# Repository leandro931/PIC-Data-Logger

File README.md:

# PIC-Data-Logger
A data logger based on PIC18F4550 for development

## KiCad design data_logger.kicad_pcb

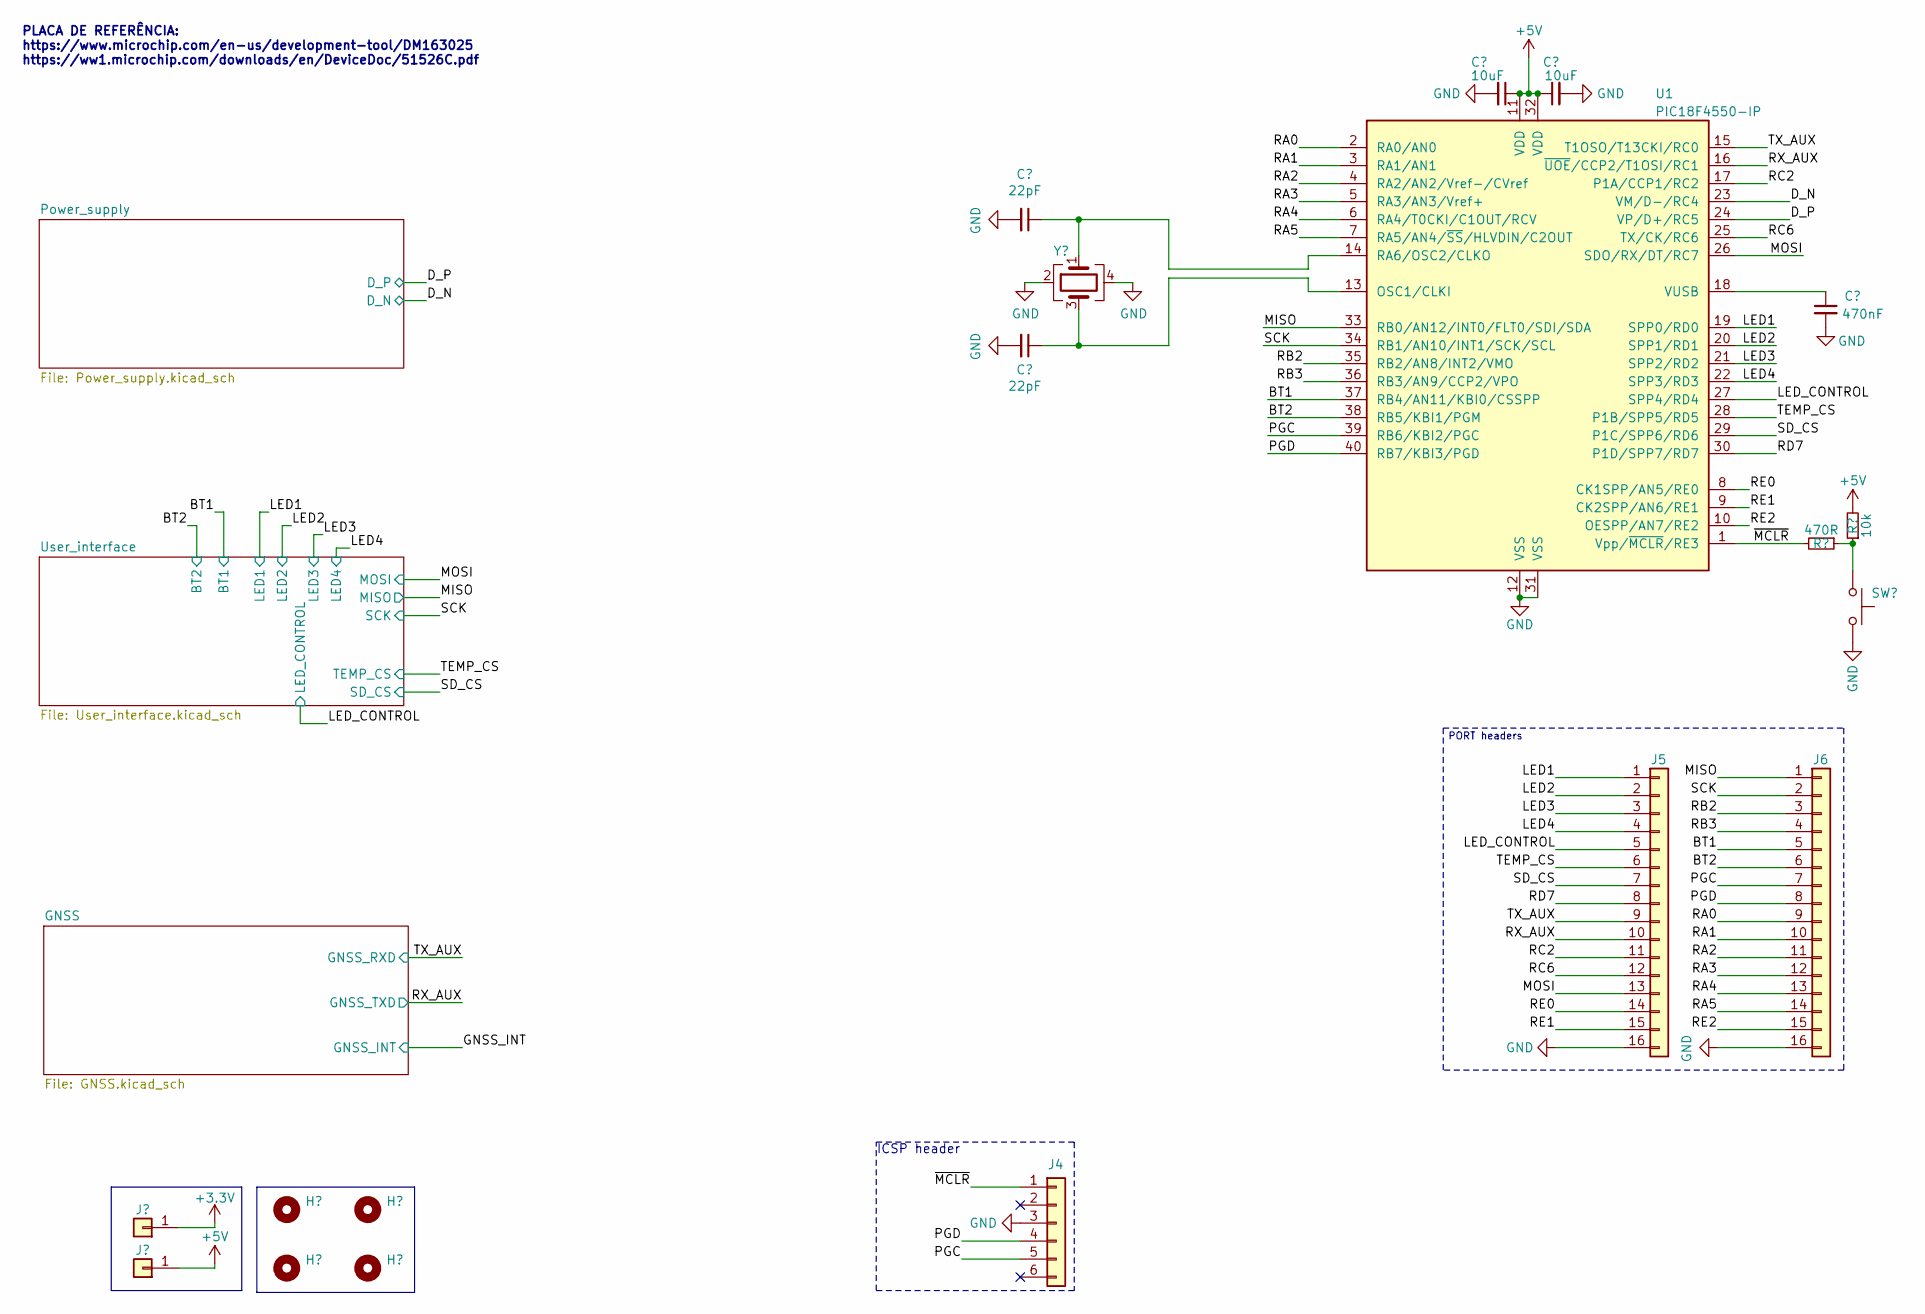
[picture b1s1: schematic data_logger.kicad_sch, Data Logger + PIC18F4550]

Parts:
C1, C2: 22pF; C_0402_1005Metric; Voltage rating greater than or equal to 50V; Tolerance less than or equal to ±1%
C3, C4: 10uF; C_0603_1608Metric; Tolerance less than or equal to ±10%; Voltage rating greater than or equal to 50V
C5: 470nF; C_0603_1608Metric; Tolerance less than or equal to ±10%; Voltage rating greater than or equal to 50V
H1, H2, H3, H4: MountingHole; MountingHole_2.2mm_M2
J1, J2: PinHeader_01x01_P2.54mm_Vertical; PinHeader_1x01_P2.54mm_Vertical
J4: PinHeader_01x06_P2.54mm_Vertical; PinHeader_1x06_P2.54mm_Vertical
J5, J6: Conn_01x16; PinSocket_1x16_P2.54mm_Vertical
R1: 470R; R_0402_1005Metric; Power rating greater than or equal to 1/10W; Tolerance less than or equal to ±5%
R2: 10k; R_0402_1005Metric; Power rating greater than or equal to 1/10W; Tolerance less than or equal to ±5%
SW1: SW_Push_Shouhan_TS3315A; SW_Push_SPST_TopActuated_Shouhan_TS3315A; Power rating 50mA@12VDC; Manufacturer P/N TS3315A; lcsc# C412367
U1: PIC18F4550-IP; DIP-40_W15.24mm
Y1: X1E0000210624; Crystal_SMD_3225-4Pin_3.2x2.5mm; Manufacturer P/N Q24FA20H00431; lcsc# C255914

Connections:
+3.3V: J1.1; also elsewhere on the board
+5V: C3.1, C4.1, J2.1, R2.2, U1.11 (VDD), U1.32 (VDD); also elsewhere on the board
/BT1: J6.5, U1.37 (RB4/AN11/KBI0/CSSPP); also elsewhere on the board
/BT2: J6.6, U1.38 (RB5/KBI1/PGM); also elsewhere on the board
/D_N: U1.23 (VM/D-/RC4); also elsewhere on the board
/D_P: U1.24 (VP/D+/RC5); also elsewhere on the board
/LED1: J5.1, U1.19 (SPP0/RD0); also elsewhere on the board
/LED2: J5.2, U1.20 (SPP1/RD1); also elsewhere on the board
/LED3: J5.3, U1.21 (SPP2/RD2); also elsewhere on the board
/LED4: J5.4, U1.22 (SPP3/RD3); also elsewhere on the board
/LED_CONTROL: J5.5, U1.27 (SPP4/RD4); also elsewhere on the board
/MISO: J6.1, U1.33 (RB0/AN12/INT0/FLT0/SDI/SDA); also elsewhere on the board
/MOSI: J5.13, U1.26 (SDO/RX/DT/RC7); also elsewhere on the board
/PGC: J4.5, J6.7, U1.39 (RB6/KBI2/PGC)
/PGD: J4.4, J6.8, U1.40 (RB7/KBI3/PGD)
/RA0: J6.9, U1.2 (RA0/AN0)
/RA1: J6.10, U1.3 (RA1/AN1)
/RA2: J6.11, U1.4 (RA2/AN2/Vref-/CVref)
/RA3: J6.12, U1.5 (RA3/AN3/Vref+)
/RA4: J6.13, U1.6 (RA4/T0CKI/C1OUT/RCV)
/RA5: J6.14, U1.7 (RA5/AN4/~SS/HLVDIN/C2OUT)
/RB2: J6.3, U1.35 (RB2/AN8/INT2/VMO)
/RB3: J6.4, U1.36 (RB3/AN9/CCP2/VPO)
/RC2: J5.11, U1.17 (P1A/CCP1/RC2)
/RC6: J5.12, U1.25 (TX/CK/RC6)
/RD7: J5.8, U1.30 (P1D/SPP7/RD7)
/RE0: J5.14, U1.8 (CK1SPP/AN5/RE0)
/RE1: J5.15, U1.9 (CK2SPP/AN6/RE1)
/RE2: J6.15, U1.10 (OESPP/AN7/RE2)
/RX_AUX: J5.10, U1.16 (~UOE/CCP2/T1OSI/RC1); also elsewhere on the board
/SCK: J6.2, U1.34 (RB1/AN10/INT1/SCK/SCL); also elsewhere on the board
/SD_CS: J5.7, U1.29 (P1C/SPP6/RD6); also elsewhere on the board
/TEMP_CS: J5.6, U1.28 (P1B/SPP5/RD5); also elsewhere on the board
/TX_AUX: J5.9, U1.15 (T1OSO/T13CKI/RC0); also elsewhere on the board
/~MCLR: J4.1, R1.2, U1.1 (Vpp/~MCLR/RE3)
GND: C1.2, C2.2, C3.2, C4.2, C5.2, J4.3, J5.16, J6.16, SW1.2, U1.12 (VSS), U1.31 (VSS), Y1.2, Y1.4; also elsewhere on the board
unnamed: R1.1, R2.1, SW1.1
unnamed: C2.1, U1.13 (OSC1/CLKI), Y1.3
unnamed: C1.1, U1.14 (RA6/OSC2/CLKO), Y1.1
unnamed: C5.1, U1.18 (VUSB)

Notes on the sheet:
ICSP header
PLACA DE REFERÊNCIA: https://www.microchip.com/en-us/development-tool/DM163025 https://ww1.microchip.com/downloads/en/DeviceDoc/51526C.pdf
PORT headers

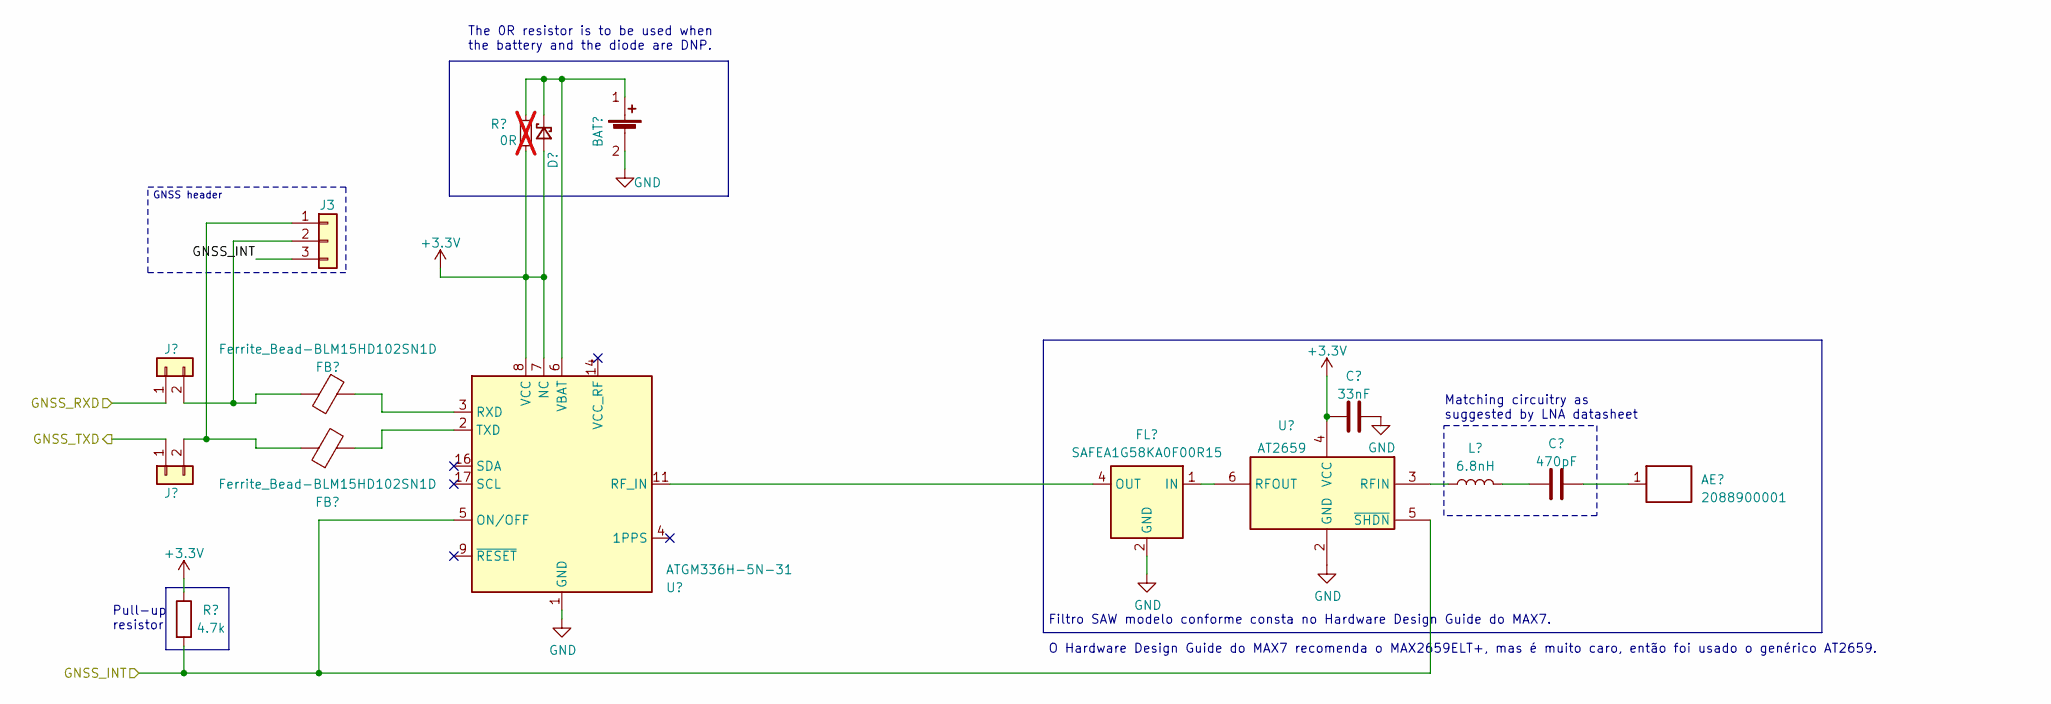
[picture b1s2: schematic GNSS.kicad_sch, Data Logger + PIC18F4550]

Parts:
AE1: 2088900001; Molex-2088900001-GPS-Ceramic_Antenna; Power rating 2W max. (CW); Manufacturer P/N 2088900001; mouser# 538-208890-0001
BAT1: Battery_Seiko_MS412FE_D4.8mm; Manufacturer P/N MS412FE-FL26E; digikey# 728-1053-ND
C6: 33nF; C_0402_1005Metric; Tolerance less than or equal to ±10%; Voltage rating greater than or equal to 16V
C7: 470pF; C_0402_1005Metric; Tolerance less than or equal to ±10%; Voltage rating greater than or equal to 16V
D1: CDBQC0240LR-HF; D_0402_1006Metric; Manufacturer P/N CDBQC0240LR-HF; digikey# 641-1888-1-ND
FB1, FB2: Ferrite_Bead-BLM15HD102SN1D; L_0402_1005Metric; Manufacturer P/N BLM15HD102SN1D
FL1: SAFEA1G58KA0F00R15; Filter_1109-5_1.1x0.9mm; Manufacturer P/N SAFEA1G58KA0F00R15; lcsc# C91641
J3: Conn_01x03; PinSocket_1x03_P2.54mm_Vertical
J7, J8: PinHeader_01x02_P2.54mm_Vertical; PinHeader_1x02_P2.54mm_Vertical
L1: 6.8nH; L_0402_1005Metric
R3: 4.7k; R_0402_1005Metric; Power rating 1/8W; Tolerance ±1%; Manufacturer P/N RS-05K4701FT; LCSC P/N C115319
R4: 0R; R_0402_1005Metric; Power rating greater than or equal to 1/16W; Tolerance Jumper; Manufacturer P/N CRCW04020000Z0ED; digikey# 541-0.0JCT-ND; not fitted
U2: ATGM336H-5N-31; atgm336h; Manufacturer P/N ATGM336H-5N31
U3: AT2659; lcsc# C92450

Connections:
+3.3V: C6.1, D1.2 (A), R3.1, R4.2, U2.7 (NC), U2.8 (VCC), U3.4 (VCC); also elsewhere on the board
/GNSS_INT: J3.3, R3.2, U2.5 (ON/OFF), U3.5 (~SHDN)
/RX_AUX: J8.1; also elsewhere on the board
/TX_AUX: J7.1; also elsewhere on the board
GND: BAT1.2 (-), C6.2, FL1.2 (GND), FL1.3 (GND), FL1.5 (GND), U2.1 (GND), U2.10 (GND), U2.12 (GND), U3.1 (GND), U3.2 (GND); also elsewhere on the board
unnamed: AE1.1, C7.2
unnamed: BAT1.1 (+), D1.1 (K), R4.1, U2.6 (VBAT)
unnamed: C7.1, L1.2
unnamed: FL1.1 (IN), U3.6 (RFOUT)
unnamed: FL1.4 (OUT), U2.11 (RF_IN)
unnamed: FB2.1, J3.1, J8.2
unnamed: FB1.2, J3.2, J7.2
unnamed: FB1.1, U2.3 (RXD)
unnamed: FB2.2, U2.2 (TXD)
unnamed: L1.1, U3.3 (RFIN)

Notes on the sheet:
Filtro SAW modelo conforme consta no Hardware Design Guide do MAX7. O Hardware Design Guide do MAX7 recomenda o MAX2659ELT+, mas é muito caro, então foi usado o genérico AT2659.
The 0R resistor is to be used when the battery and the diode are DNP.
Matching circuitry as suggested by LNA datasheet
Pull-up resistor
GNSS header

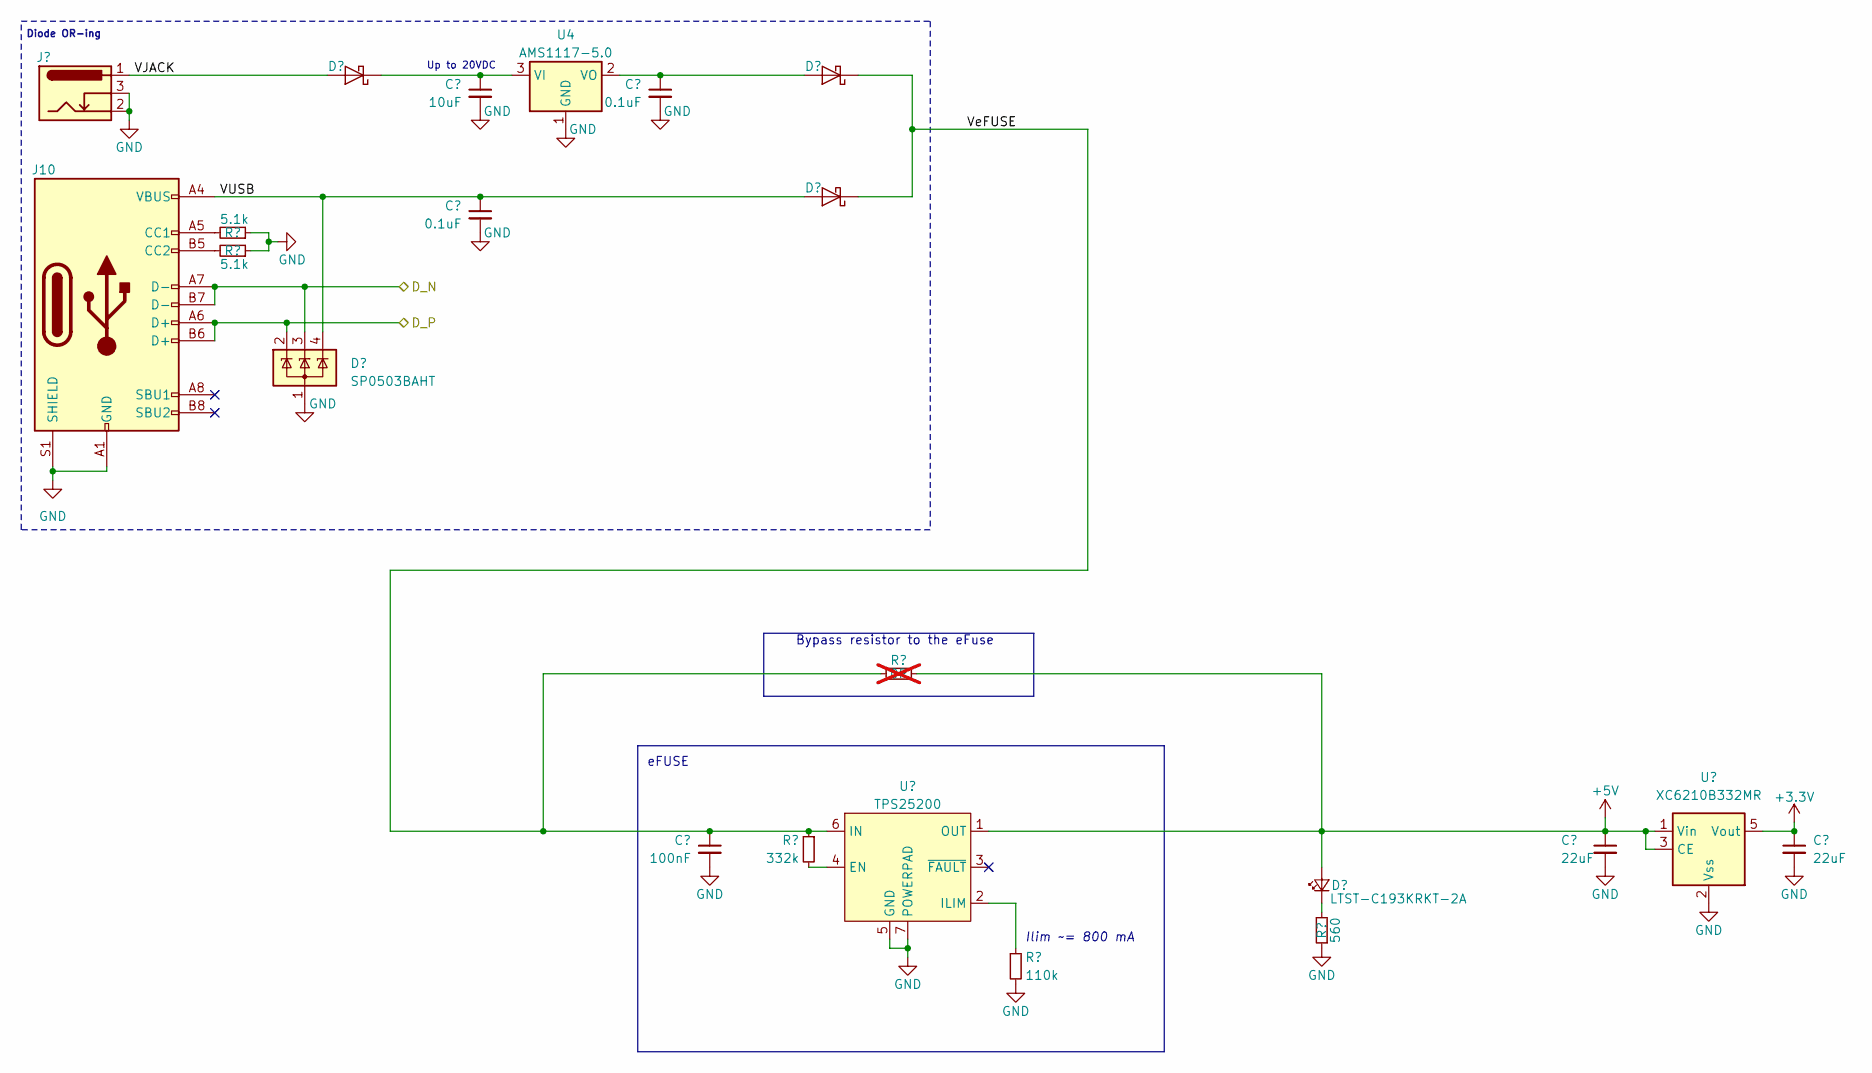
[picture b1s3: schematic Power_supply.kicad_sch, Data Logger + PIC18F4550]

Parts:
C8: 10uF; C_0603_1608Metric; Tolerance less than or equal to ±10%; Voltage rating greater than or equal to 50V
C9, C10: 0.1uF; C_0603_1608Metric; Tolerance less than or equal to ±10%; Voltage rating greater than or equal to 50V
C11: 100nF; C_0603_1608Metric; Tolerance less than or equal to ±10%; Voltage rating greater than or equal to 50V; Manufacturer P/N 08055C104KAT2A; digikey# 478-1395-1-ND
C12, C13: 22uF; C_0603_1608Metric; Tolerance less than or equal to ±20%; Voltage rating greater than or equal to 16V; Manufacturer P/N 1206YD226MAT2A; digikey# 478-5332-1-ND
D2: SP0503BAHT; SOT-143
D3, D4, D5: DSK24_K24; Microdiode_SOD-123FL; Manufacturer P/N DSK24 K24; lcsc# C64890
D6: LTST-C193KRKT-2A; LED_0603_1608Metric; Manufacturer P/N LTST-C193KRKT-2A; digikey# 160-1909-1-ND
J9: Barrel_Jack_Switch_CUI_PJ-102AH; BarrelJack_CUI_PJ-102AH_Horizontal; Manufacturer P/N PJ-102AH; digikey# CP-102AH-ND
J10: USB_C_Receptacle; USB_C_Receptacle_GCT_USB4105-xx-A_16P_TopMnt_Horizontal; Manufacturer P/N KH-TYPE-C-16P; lcsc# C709357
R5, R6: 5.1k; R_0603_1608Metric; Power rating greater than or equal to 1/10W; Tolerance less than or equal to ±1%; Manufacturer P/N CRCW0603332KFKEA; digikey# 541-332KHCT-ND
R7: 332k; R_0603_1608Metric; Power rating greater than or equal to 1/10W; Tolerance less than or equal to ±1%; Manufacturer P/N CRCW0603332KFKEA; digikey# 541-332KHCT-ND
R8: 0R; R_0805_2012Metric; Power rating greater than or equal to 1/8W; Tolerance Jumper; Manufacturer P/N RMCF0805ZT0R00; digikey# RMCF0805ZT0R00CT-ND; not fitted
R9: 110k; R_0805_2012Metric; Power rating greater than or equal to 1/8W; Tolerance less than or equal to ±0,1%; Manufacturer P/N RT0805BRD07169KL; digikey# YAG4836CT-ND
R10: 560; R_0402_1005Metric; Power rating greater than or equal to 1/10W; Tolerance less than or equal to ±5%; Manufacturer P/N RC0603JR-072KL; digikey# 311-2.0KGRCT-ND
U4: AMS1117-5.0; SOT-223-3_TabPin2
U5: TPS25200; Texas_DRV0006A_WSON-6-1EP_2x2mm_P0.65mm_EP1x1.6mm_ThermalVi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; Manufacturer P/N TPS25200DRVR; digikey# 296-37842-1-ND
U6: XC6210B332MR; Torex_SOT-25; Manufacturer P/N XC6210B332MR; digikey# 893-1075-1-ND

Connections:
+3.3V: C13.1, U6.5 (Vout); also elsewhere on the board
+5V: C12.1, D6.2 (A), R8.2, U5.1 (OUT), U6.1 (Vin), U6.3 (CE); also elsewhere on the board
/D_N: D2.3 (K), J10.A7 (D-), J10.B7 (D-); also elsewhere on the board
/D_P: D2.2 (K), J10.A6 (D+), J10.B6 (D+); also elsewhere on the board
/Power_supply/VJACK: D3.2 (A), J9.1
/Power_supply/VUSB: C9.1, D2.4 (K), D5.2 (A), J10.A4 (VBUS), J10.A9 (VBUS), J10.B4 (VBUS), J10.B9 (VBUS)
/Power_supply/VeFUSE: C11.1, D4.1 (K), D5.1 (K), R7.1, R8.1, U5.6 (IN)
GND: C8.2, C9.2, C10.2, C11.2, C12.2, C13.2, D2.1 (A), J9.2, J9.3, J10.A1 (GND), J10.A12 (GND), J10.B1 (GND), J10.B12 (GND), J10.S1 (SHIELD), R5.1, R6.1, R9.2, R10.1, U4.1 (GND), U5.5 (GND), U5.7 (POWERPAD), U6.2 (Vss); also elsewhere on the board
unnamed: C8.1, D3.1 (K), U4.3 (VI)
unnamed: C10.1, D4.2 (A), U4.2 (VO)
unnamed: D6.1 (K), R10.2
unnamed: J10.A5 (CC1), R5.2
unnamed: J10.B5 (CC2), R6.2
unnamed: R7.2, U5.4 (EN)
unnamed: R9.1, U5.2 (ILIM)

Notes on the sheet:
eFUSE
Ilim ~= 800 mA
Up to 20VDC
Diode OR-ing
Bypass resistor to the eFuse

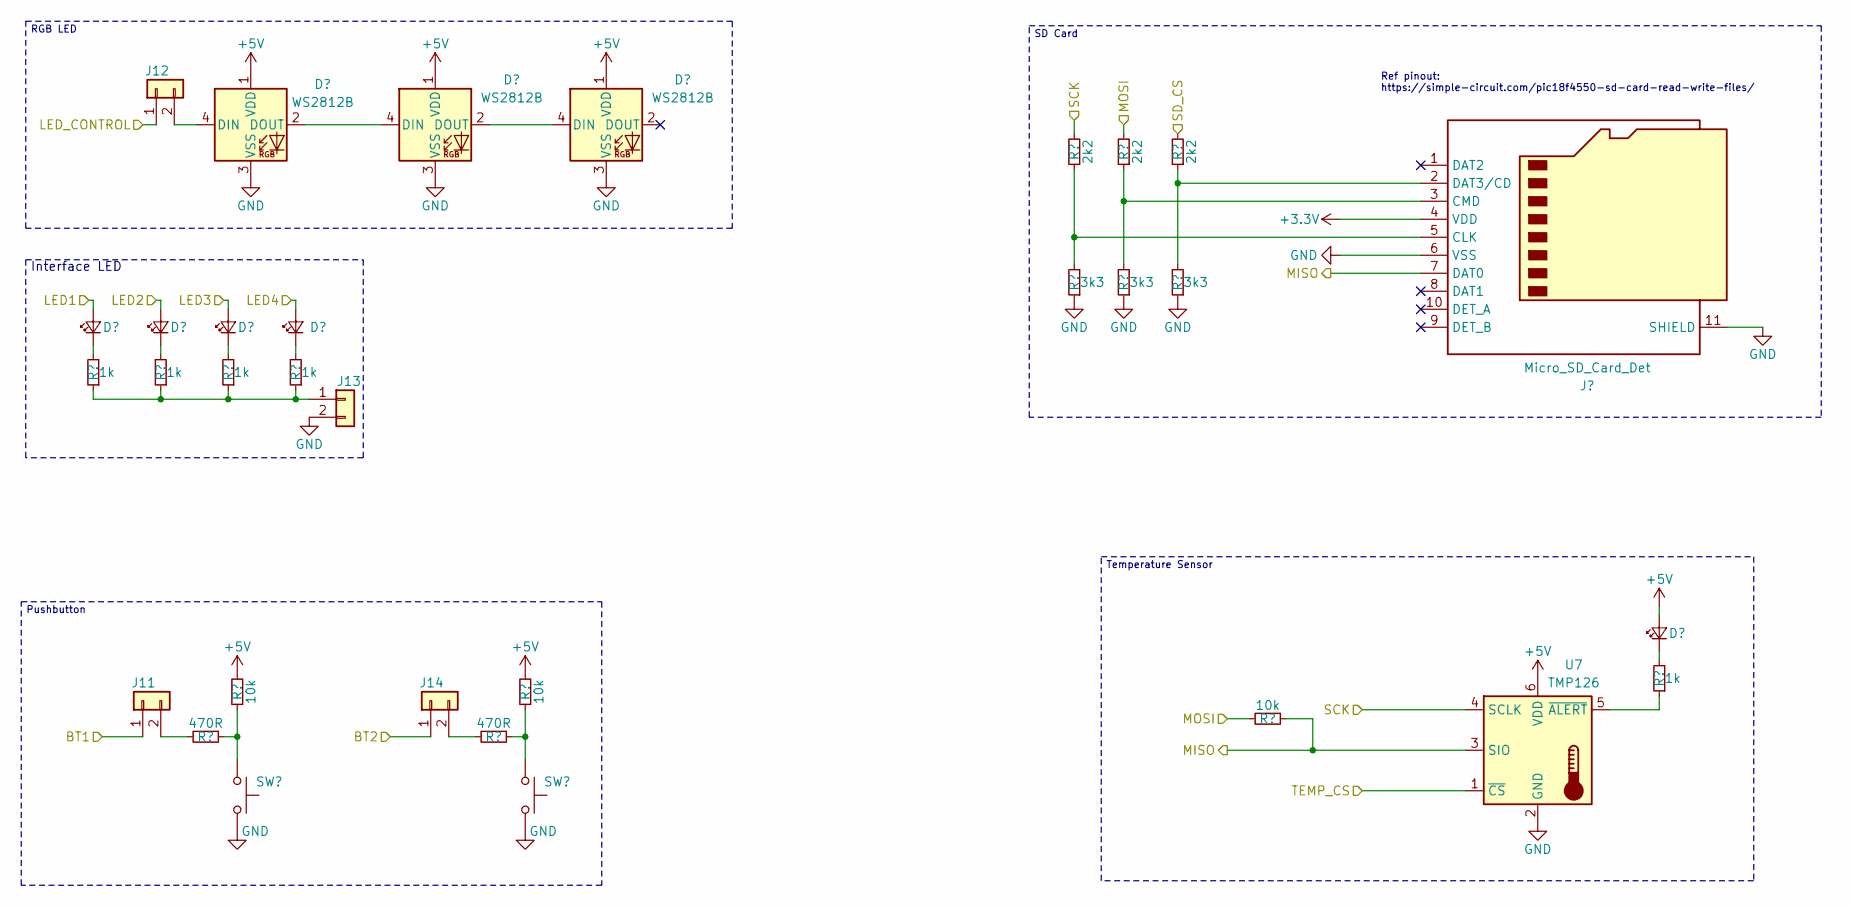
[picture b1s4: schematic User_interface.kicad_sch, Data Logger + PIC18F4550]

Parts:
D7, D8, D9, D10, D14: LTST-C193KRKT-2A; LED_0603_1608Metric; Manufacturer P/N LTST-C193KRKT-2A; digikey# 160-1909-1-ND
D11, D12, D13: WS2812B; LED_WS2812B_PLCC4_5.0x5.0mm_P3.2mm; Manufacturer P/N WS2812B
J11, J12, J13, J14: PinHeader_01x02_P2.54mm_Vertical; PinHeader_1x02_P2.54mm_Vertical
J15: Micro_SD_Card_Det; SDCARD_MOLEX_503398-1892; Manufacturer P/N 503398-1892; digikey# WM11190CT-ND
R11, R12, R14, R16, R26: 1k; R_0402_1005Metric; Power rating greater than or equal to 1/10W; Tolerance less than or equal to ±5%
R13, R17: 470R; R_0402_1005Metric; Power rating greater than or equal to 1/10W; Tolerance less than or equal to ±5%
R15, R18: 10k; R_0402_1005Metric; Power rating greater than or equal to 1/10W; Tolerance less than or equal to ±5%
R19, R21, R23: 2k2; R_0805_2012Metric; Power rating greater than or equal to 1/8W; Tolerance Jumper
R20, R22, R24: 3k3; R_0402_1005Metric; Power rating greater than or equal to 1/10W; Tolerance less than or equal to ±5%
R25: 10k; R_0805_2012Metric; Power rating greater than or equal to 1/8W; Tolerance Jumper
SW2, SW3: SW_Push_Shouhan_TS3315A; SW_Push_SPST_TopActuated_Shouhan_TS3315A; Power rating 50mA@12VDC; Manufacturer P/N TS3315A; lcsc# C412367
U7: TMP126; pSemi_SC-70-6; Manufacturer # TMP126

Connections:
+3.3V: J15.4 (VDD); also elsewhere on the board
+5V: D11.1 (VDD), D12.1 (VDD), D13.1 (VDD), D14.2 (A), R15.2, R18.2, U7.6 (VDD); also elsewhere on the board
/BT1: J11.1; also elsewhere on the board
/BT2: J14.1; also elsewhere on the board
/LED1: D7.2 (A); also elsewhere on the board
/LED2: D8.2 (A); also elsewhere on the board
/LED3: D9.2 (A); also elsewhere on the board
/LED4: D10.2 (A); also elsewhere on the board
/LED_CONTROL: J12.1; also elsewhere on the board
/MISO: J15.7 (DAT0), R25.1, U7.3 (SIO); also elsewhere on the board
/MOSI: R21.2, R25.2; also elsewhere on the board
/SCK: R19.2, U7.4 (SCLK); also elsewhere on the board
/SD_CS: R23.2; also elsewhere on the board
/TEMP_CS: U7.1 (~CS); also elsewhere on the board
GND: D11.3 (VSS), D12.3 (VSS), D13.3 (VSS), J13.2, J15.6 (VSS), J15.11 (SHIELD), R20.1, R22.1, R24.1, SW2.2, SW3.2, U7.2 (GND); also elsewhere on the board
unnamed: D7.1 (K), R11.2
unnamed: D8.1 (K), R12.2
unnamed: D9.1 (K), R14.2
unnamed: D10.1 (K), R16.2
unnamed: D11.4 (DIN), J12.2
unnamed: D11.2 (DOUT), D12.4 (DIN)
unnamed: D12.2 (DOUT), D13.4 (DIN)
unnamed: D14.1 (K), R26.2
unnamed: J11.2, R13.2
unnamed: J13.1, R11.1, R12.1, R14.1, R16.1
unnamed: J14.2, R17.2
unnamed: J15.5 (CLK), R19.1, R20.2
unnamed: J15.3 (CMD), R21.1, R22.2
unnamed: J15.2 (DAT3/CD), R23.1, R24.2
unnamed: R13.1, R15.1, SW2.1
unnamed: R17.1, R18.1, SW3.1
unnamed: R26.1, U7.5 (~ALERT)

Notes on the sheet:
Pushbutton
Ref pinout: https://simple-circuit.com/pic18f4550-sd-card-read-write-files/
Interface LED
Temperature Sensor
SD Card
RGB LED

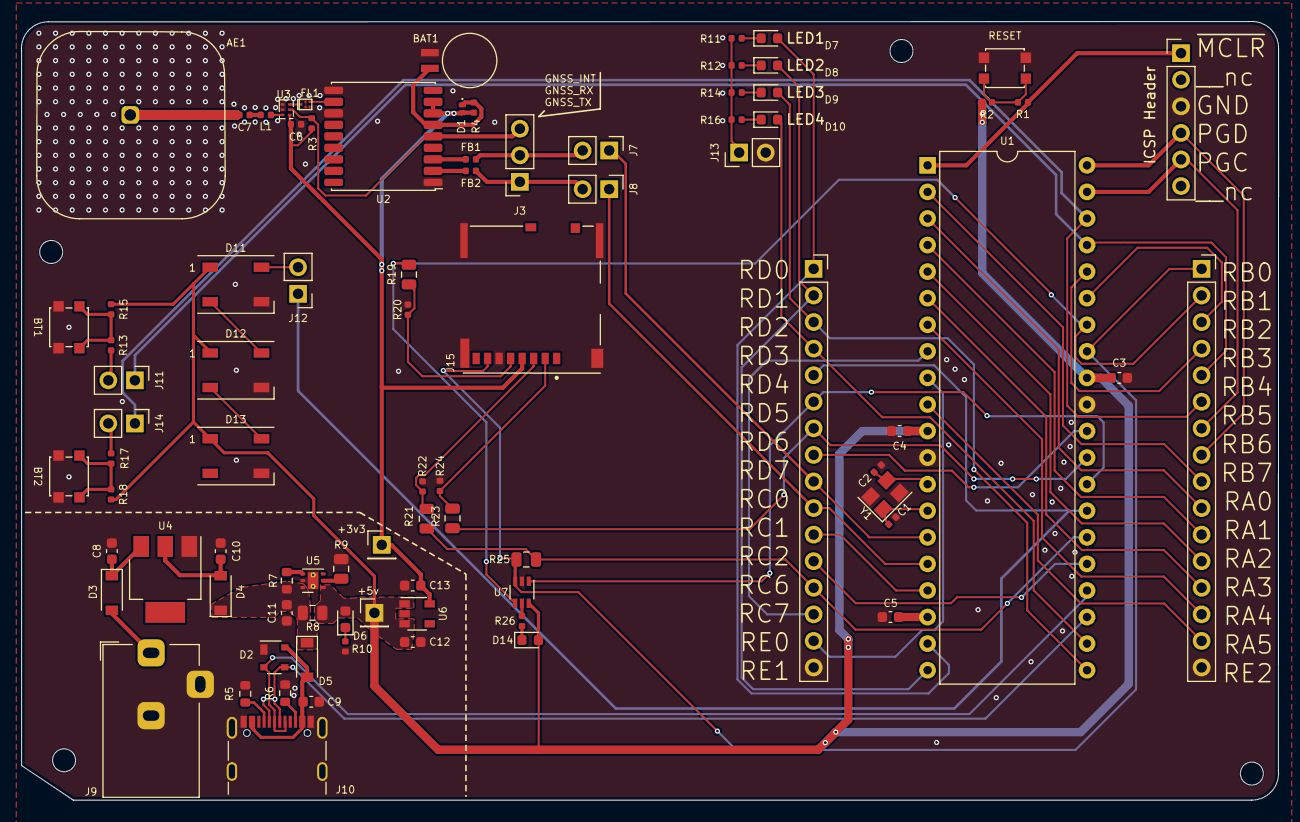
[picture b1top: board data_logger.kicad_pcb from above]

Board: 2 copper layers, 120.2 x 74.4 mm, 89 parts (0 on the bottom side), 78 nets.

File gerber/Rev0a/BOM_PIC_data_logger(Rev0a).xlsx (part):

Item | Qty | Reference(s) | To be assembled? | Value | Description | Manufacturer | Manufacturer P/N | Mounting type | Package | digikey# | lcsc# | mouser# | newark# | rs# | tme# | Datasheet
1 | 1 | AE1 | Yes | 2088900001 | GPS Ceramic Patch Antenna | Molex | 2088900001 |  |  | WM26214-ND |  | 538-208890-0001 | 84AC5252 |  |  | https://www.molex.com/content/dam/molex/molex-dot-com/produc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 | https://pt.aliexpress.com/item/1005004484929374.html?spm=a2g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
2 | 1 | BAT1 | Yes | MS412FE-FL26E | Coin, 4.8mm 3V Lithium Rechargeable Battery 1mAh (MS412FE is not reflowable. Pl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 | Seiko Instruments | MS412FE-FL26E | SMD |  | 728-1053-ND |  | 628-MS412FE-FL26E |  |  |  | https://www.sii.co.jp/en/me/datasheets/ms-rechargeable/ms412fe-5/
3 | 2 | C1, C2 | Yes | 22pF | Multilayer Ceramic Chip Capacitor 22pF | YAGEO | CC0402JRNPO7BN220 | SMD | 0402_1005Metric |  | C2175872 |  |  |  |  | https://datasheet.lcsc.com/lcsc/2202040800_YAGEO-CC0402JRNPO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
4 | 3 | C3, C4, C8 | Yes | 10uF | Multilayer Ceramic Chip Capacitor 10uF | YAGEO | CC0603MRX5R7BB106 | SMD | 0603_1608Metric |  | C109457 |  |  |  |  | https://datasheet.lcsc.com/lcsc/1811021340_YAGEO-CC0603MRX5R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
5 | 1 | C5 | Yes | 470nF | Multilayer Ceramic Chip Capacitor 470nF | YAGEO | CC0603KRX7R7BB474 | SMD | 0603_1608Metric |  | C106851
6 | 1 | C6 | Yes | 33nF | Multilayer Ceramic Chip Capacitor 33nF | YAGEO | CC0402FRNPO9BN330 | SMD | 0402_1005Metric |  | C327064
7 | 1 | C7 | Yes | 470pF | Multilayer Ceramic Chip Capacitor 470pF | YAGEO | CC0402JRNPO7BN471 | SMD | 0402_1005Metric |  | C526993
8 | 2 | C9, C10 | Yes | 0.1uF | Multilayer Ceramic Chip Capacitor 0.1uF | YAGEO | CS0603KRX7R8BB104 | SMD | 0603_1608Metric |  | C577419
9 | 1 | C11 | Yes | 100nF | Multilayer Ceramic Chip Capacitor 100nF | YAGEO | CC0603KRX7R9BB104 | SMD | 0603_1608Metric |  | C14663
10 | 2 | C12, C13 | Yes | 22uF | Multilayer Ceramic Chip Capacitor 22uF | YAGEO | CC0603MRX5R5BB226 | SMD | 0603_1608Metric |  | C109448
11 | 1 | D1 | Yes | CDBQC0240LR-HF | Diode 40 V 200mA Surface Mount 0402C/SOD-923F | Comchip Technology | CDBQC0240LR-HF | SMD | 0402/SOD-923F | 641-1888-2-ND | C3758513 |  |  |  |  | https://www.comchiptech.com/admin/files/product/CDBQC0240LR-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
12 | 1 | D2 | Yes | SP0503BAHTG | 8.5V Clamp Ipp Tvs Diode Surface Mount SOT-143-4 | Littelfuse | SP0503BAHTG | SMD | SOT-143 | SP0503BAHT-ND | C7074 |  |  |  |  | http://www.littelfuse.com/~/media/files/littelfuse/technical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
13 | 3 | D3, D4, D5 | Yes | DSK24 | Schottky Barrier Diodes 40V 2A 550mV @ 2A SOD-123FL | MDD (Microdiode Electronics) | DSK24 | SMD | SOD-123FL | 3372-DSK24TR-ND | C64890 |  |  |  |  | https://mm.digikey.com/Volume0/opasdata/d220001/medias/docus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
14 | 1 | D6 | Yes | LTST-C193KRKT-2A | LED (red) 0603_1608Metric | Lite-On Inc. | LTST-C193KRKT-2A | SMD | 0603_1608 | 160-1909-1-ND |  |  |  |  |  | https://mm.digikey.com/Volume0/opasdata/d220001/medias/docus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
15 | 4 | D7, D8, D9, D10 | Yes | LTST-C193TBKT-5A | LED (blue) 0603_1608Metric | Lite-On Inc. |  | SMD | 0603_1608 | 160-1827-6-ND | C125103
16 | 3 | D11, D12, D13 | Yes | WS2812B | Intelligent control LED | Wordlsemi | WS2812B | SMD | SMD5050 | 1568-COM-16347TR-ND | C2761795 |  |  |  |  | https://cdn-shop.adafruit.com/datasheets/WS2812B.pdf
17 | 1 | D14 | Yes | LTST-C190YKT | LED (yellow) 0603_1608Metric | Lite-On Inc. | LTST-C190YKT | SMD | 0603_1608 | 160-1184-6-ND | C125097
18 | 2 | FB1, FB2 | Yes | Ferrite_Bead-BLM15HD102SN1D | 1kÎ© @ 100MHz 250mA 1 1.25Î© 0402 Ferrite Beads RoHS | Murata Electronics | BLM15HD102SN1D | SMD | 0402_1005 | 490-4003-2-ND | C21516 | 81-BLM15HD102SN1D |  |  |  | https://datasheet.lcsc.com/szlcsc/1811091923_Murata-Electron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
19 | 1 | FL1 | Yes | SAFEA1G58KA0F00R15 | GNSS SAW filter | Murata | SAFEA1G58KA0F00R15 | SMD | QCS5P |  | C91641 |  |  |  |  | https://datasheet.lcsc.com/lcsc/1810161815_Murata-Electronic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
20 | 4 | H1, H2, H3, H4 | Not applicable | MountingHole | Mounting hole |  |  |  |  |  |  |  |  |  |  | ~
21 | 2 | J1, J2 | No | PinHeader_01x01_P2.54mm_Vertical | Pin header, single row, 01x01, 1.27mm pitch, vertical |  |  | PTH |  |  |  |  |  |  |  | ~
22 | 1 | J3 | Yes | PinHeader_01x03_P2.54mm | PinHeader_01x03_P2.54mm |  |  | PTH |  |  |  |  |  |  |  | ~
23 | 1 | J4 | Yes | PinHeader_01x06_P2.54mm | PinHeader_01x06_P2.54mm |  |  | PTH |  |  |  |  |  |  |  | ~
24 | 2 | J5, J6 | Yes | PinHeader_01x16_P2.54mm | PinHeader_01x16_P2.54mm |  |  | PTH |  |  |  |  |  |  |  | ~
25 | 6 | J7, J8, J11, J12, J13, J14 | Yes | PinHeader_01x02_P2.54mm | PinHeader_01x02_P2.54mm |  |  | PTH |  |  |  |  |  |  |  | ~
26 | 1 | J9 | Yes | Barrel_Jack_Switch_CUI_PJ-102AH | DC Power Jack with an internal switch | CUI Devices | PJ-102AH | PTH |  | CP-102AH-ND |  | 490-PJ-102AH |  |  |  | https://www.cuidevices.com/product/resource/pj-102ah.pdf
27 | 1 | J10 | Yes | USB_C_Receptacle | USB Type-C Receptacle 16-pin connector | Shenzhen Kinghelm Elec | KH-TYPE-C-16P | SMD |  |  | C709357 |  |  |  |  | https://datasheet.lcsc.com/lcsc/2009111434_Shenzhen-Kinghelm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
28 | 1 | J15 | Yes | 5033981892 | 1.10mm Pitch microSD Memory Card Connector, Normal Mount Surface Mount, PushPus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 | Molex | 503398-1892 | SMD |  | WM11190CT-ND | C428492 |  | 35X2791 | 880-1277 | MX-503398-1892 | https://www.molex.com/pdm_docs/sd/5033981892_sd.pdf
29 | 1 | L1 | Yes | 6.8nH | Inductor 6.8nH | Murata | LQG15HH6N8J02D | SMD | 0402_1005Metric |  | C440214
30 | 3 | R1, R13, R17 | Yes | 470R | Chip Resistor 470R |  |  | SMD | 0402_1005Metric
31 | 3 | R2, R15, R18 | Yes | 10k | Chip Resistor 10k |  |  | SMD | 0402_1005Metric
32 | 1 | R3 | Yes | 4.7k | Chip Resistor 4.7k |  |  | SMD | 0402_1005Metric
33 | 1 | R4 | No | 0R | Chip Resistor 0R |  |  | SMD | 0402_1005Metric
34 | 2 | R5, R6 | Yes | 5.1k | Chip Resistor 5.1k |  |  | SMD | 0603_1608Metric
35 | 1 | R7 | Yes | 332k | Chip Resistor 332k |  |  | SMD | 0603_1608Metric
36 | 1 | R8 | No | 0R | Chip Resistor 0R |  |  | SMD | 0805_2012Metric
37 | 1 | R9 | Yes | 110k | Chip Resistor 110k |  |  | SMD | 0805_2012Metric
38 | 1 | R10 | Yes | 560 | Chip Resistor 560 |  |  | SMD | 0402_1005Metric
39 | 5 | R11, R12, R14, R16, R26 | Yes | 1k | Chip Resistor 1k |  |  | SMD | 0402_1005Metric
40 | 3 | R19, R21, R23 | Yes | 2k2 | Chip Resistor 2k2 |  |  | SMD | 0805_2012Metric |  |  |  |  |  |  | https://www.seielect.com/catalog/sei-rmcf_rmcp.pdf
41 | 3 | R20, R22, R24 | Yes | 3k3 | Chip Resistor 3k3 |  |  | SMD | 0402_1005Metric |  |  |  |  |  |  | https://www.yageo.com/upload/media/product/productsearch/dat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
42 | 1 | R25 | Yes | 10k | Chip Resistor 10k |  |  | SMD | 0805_2012Metric |  |  |  |  |  |  | https://www.seielect.com/catalog/sei-rmcf_rmcp.pdf
43 | 3 | SW1, SW2, SW3 | Yes | SW_Push_Shouhan_TS3315A | Tactile Switch SPST 50mA@12VDC Top Actuated Round Button 5N SMD, 3.3x3.3x1.5mm | Shou Han (Shenzhen Shouhan Technology) | TS3315A | SMD |  |  | C412367 |  |  |  |  | https://datasheet.lcsc.com/lcsc/1912111437_SHOU-HAN-TS3315A_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
44 | 1 | U1 | Yes | PIC18F4550-I/P |  | Microchip | PIC18F4550-I/P | PTH | DIP-40 |  | C648001 |  |  |  |  | http://ww1.microchip.com/downloads/en/DeviceDoc/39760d.pdf
52 |  | U1 | Yes | IC Socket DIP-40 | 40P DIP Square Holes 2.54mm | Cvilux | CS054011A0A | PTH | DIP-40 |  | C918631
45 | 1 | U2 | Yes | ATGM336H-5N32 | Satellite Positioning Module | ZHONGKEWEI | ATGM336H-5N32 | SMD |  |  | C5117921 |  |  |  |  | https://www.icofchina.com/d/file/xiazai/2016-12-05/b5c57074f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
46 | 1 | U3 | Yes | AT2659 | Low Noise Amplifiers | ZHONGKEWEI | AT2659 | SMD |  |  | C92450 |  |  |  |  | https://datasheet.lcsc.com/lcsc/1810010517_ZHONGKEWEI-AT2659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
47 | 1 | U4 | Yes | AMS1117-5.0 | 1A Fixed 5V Positive Linear Voltage Regulators (LDO) | Advanced Monolithic Systems | AMS1117-5.0 | SMD | SOT-223 |  | C6187 |  |  |  |  | https://datasheet.lcsc.com/lcsc/2309181408_Advanced-Monolith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

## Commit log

2023-11-16 Teste de commit pelo VS Code
2023-11-20 Inclusão dos arquivos de fabricação para 1ª cotação
2024-11-20 Menores ajustes
